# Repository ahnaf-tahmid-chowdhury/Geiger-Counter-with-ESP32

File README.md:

# SmartGeiger

>Development of background radiation monitoring with IoT based device

## Objectives

- Flash ESP32 with Micropython
- Setup 400v voltage output to count radioactivity from SBM-20 with 4.5M MΩ series resistor
- Measures radioactive gamma and beta and alpha radiation with quite good resolution
- Use of shields to detect particles
- Use of ULTRASONIC SENSOR to detect location of the sample
- Collcet the data from the serial and then add them to a list of array by using python script
- Use of MQTTClient to pass the observed data to network
- Use of Node-RED to programe for wiring together hardware devices, APIs and online services in new and interesting ways.

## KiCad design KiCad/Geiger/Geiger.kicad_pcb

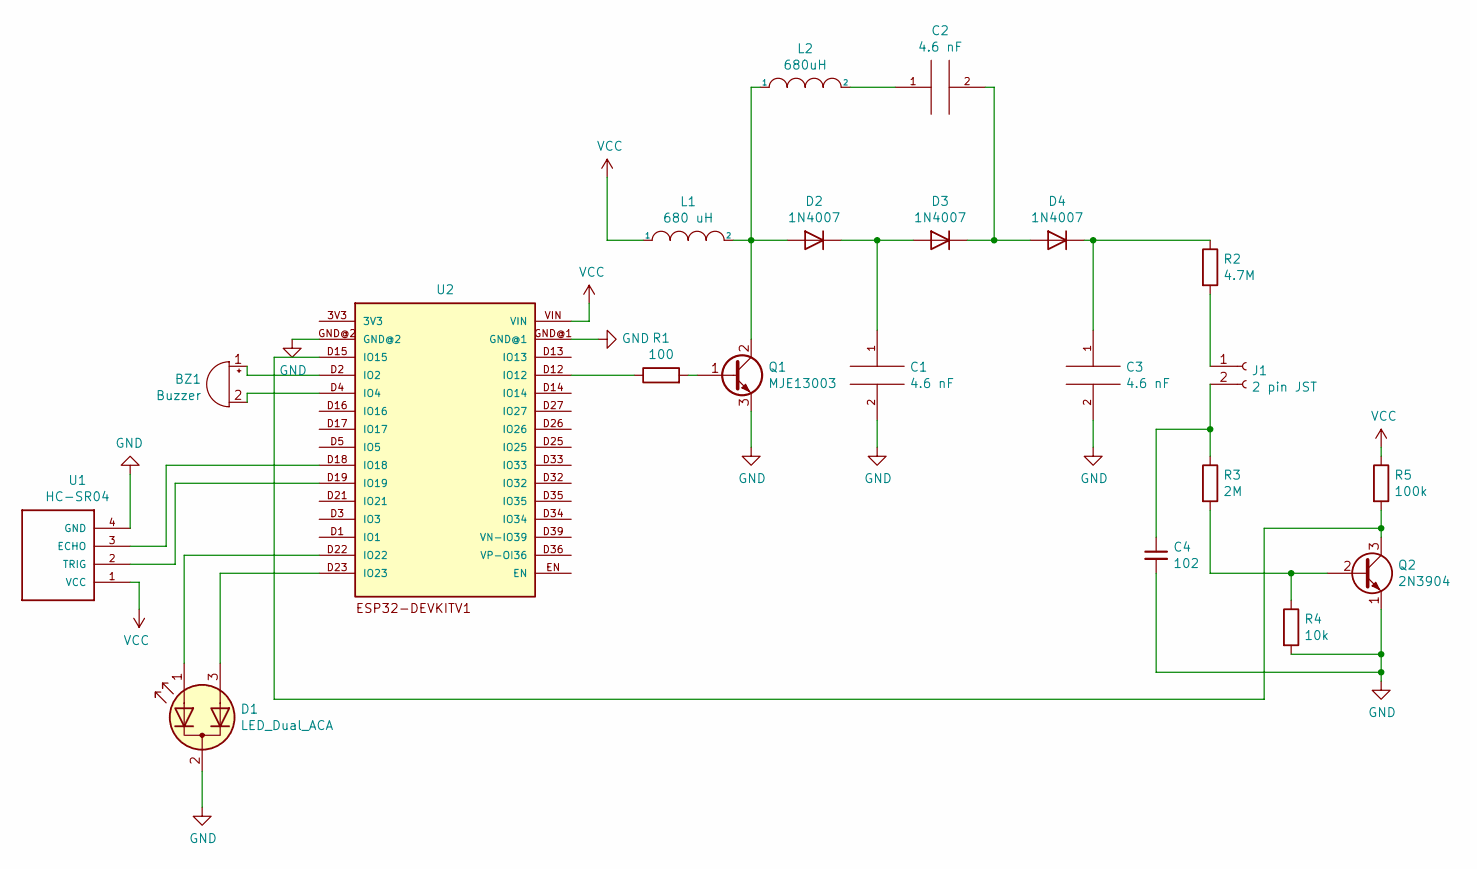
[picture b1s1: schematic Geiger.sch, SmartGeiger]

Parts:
BZ1: Buzzer; Buzzer_12x9.5RM7.6
C1, C2, C3: 4.6 nF; C_Rect_L13.0mm_W4.0mm_P10.00mm_FKS3_FKP3_MKS4
C4: 102; C_Disc_D3.4mm_W2.1mm_P2.50mm
D1: LED_Dual_ACA; LED_D5.0mm-3
D2, D3, D4: 1N4007; D_DO-41_SOD81_P10.16mm_Horizontal
J1: 2 pin JST; JST_EH_B2B-EH-A_1x02_P2.50mm_Vertical
L1: 680 uH; L_Axial_L9.5mm_D4.0mm_P15.24mm_Horizontal_Fastron_SMCC
L2: 680uH; L_Axial_L9.5mm_D4.0mm_P15.24mm_Horizontal_Fastron_SMCC
Q1: MJE13003; TO-126-3_Vertical
Q2: 2N3904; TO-92_Inline
R1: 100; R_Axial_DIN0207_L6.3mm_D2.5mm_P10.16mm_Horizontal
R2: 4.7M; R_Axial_DIN0207_L6.3mm_D2.5mm_P10.16mm_Horizontal
R3: 2M; R_Axial_DIN0207_L6.3mm_D2.5mm_P10.16mm_Horizontal
R4: 10k; R_Axial_DIN0207_L6.3mm_D2.5mm_P10.16mm_Horizontal
R5: 100k; R_Axial_DIN0207_L6.3mm_D2.5mm_P10.16mm_Horizontal
U1: HC-SR04; XCVR_HC-SR04
U2: ESP32DEVKITV1; ESP32-DEVKITV1

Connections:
GND: C1.2, C3.2, C4.2, D1.2 (K), Q1.3 (E), Q2.1 (E), R4.2, U1.4 (GND), U2.GND@1, U2.GND@2
unnamed: BZ1.1 (-), U2.D2 (IO2)
unnamed: BZ1.2 (+), U2.D4 (IO4)
unnamed: C1.1, D2.1 (K), D3.2 (A)
unnamed: C2.1, L2.2
unnamed: C2.2, D3.1 (K), D4.2 (A)
unnamed: C3.1, D4.1 (K), R2.1
unnamed: C4.1, J1.2, R3.1
unnamed: D1.1 (A1), U2.D22 (IO22)
unnamed: D1.3 (A2), U2.D23 (IO23)
unnamed: D2.2 (A), L1.2, L2.1, Q1.2 (C)
unnamed: J1.1, R2.2
unnamed: Q1.1 (B), R1.2
unnamed: Q2.2 (B), R3.2, R4.1
unnamed: Q2.3 (C), R5.2, U2.D15 (IO15)
unnamed: R1.1, U2.D12 (IO12)
unnamed: U1.2 (TRIG), U2.D19 (IO19)
unnamed: U1.3 (ECHO), U2.D18 (IO18)
VCC: L1.1, R5.1, U1.1 (VCC), U2.VIN

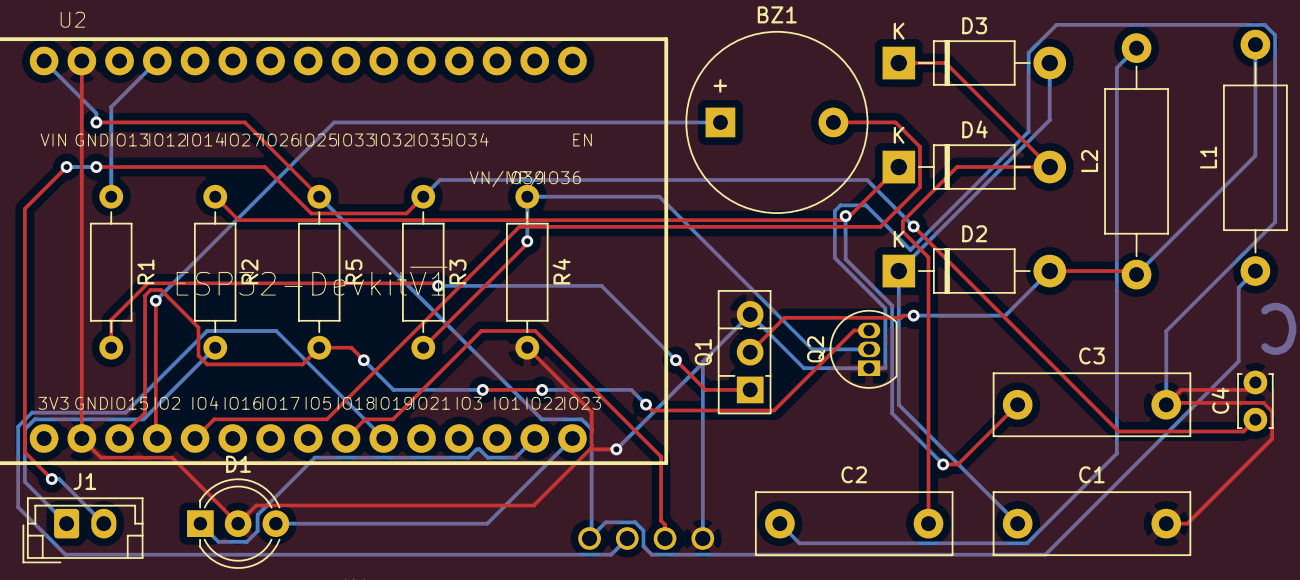
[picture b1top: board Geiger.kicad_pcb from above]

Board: 2 copper layers, 21 parts (0 on the bottom side), 19 nets.

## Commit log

2020-09-15 wlan config created
2020-09-21 Create README.md
    the project is in process
2020-09-21 moved files to folders
2020-09-21 bug fix
2020-09-21 data updated
2020-09-21 data update
2020-09-22 files updated. buzzer,geiger,main.py added
2020-09-22 node red added
2020-09-27 time added to print
2020-09-27 serial data to csv
2020-09-27 3d plot. not completed
2020-09-27 this is csv which is created by running csv3d
2020-10-29 esp debug turned off
2020-10-29 class added
2020-10-29 collected from https://github.com/HowManyOliversAreThere/hx711_mpy-driver.git
2020-10-29 merged with geiger.py
2020-10-29 removed Buzzer and Geiger and geiger added
2020-10-29 micropython/__pycache__/geiger.cpython-38.pyc
2021-03-04 ftp and ultrasonic sensor added
2021-03-04 removed
2021-03-04 upip.install('micropython-uasyncio')
2021-03-04 Asynchronous Programming with uasyncio
2021-03-04 set buzzer sleep time to 10 us
2021-03-04 low cpm is devided by 2 for getting double count
2021-03-04 lower cpm is devided by 2
2021-03-06 PCB for SmartGeiger created
2021-03-10 SmartGeiger
2021-03-10 3d obj added
2021-03-12 json file will read and saved to config variable
2021-03-12 config file
2021-03-12 Simple wlan connection setup
2021-03-12 local and cloud MQTT, json config, msg alert
2021-03-13 buzzer off function
2021-03-16 marge up things
2021-03-17 BiColorLED added, freq added
2021-03-17 fix local publish
2021-03-17 Node RED file update
2021-03-17 waln ip config check add
2021-03-18 remove machine PWM
2021-03-28 remove d1 and marge with event
2021-06-27 Create LICENSE
2021-07-26 Add title

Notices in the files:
KiCad/Geiger/Geiger.kicad_pcb:
License: CC BY 4.0
KiCad/Geiger/Geiger.sch:
https://creativecommons.org/licenses/by/4.0
